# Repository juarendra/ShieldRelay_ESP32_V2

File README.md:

# ShieldRelay_ESP32
Multiple Relay with ESP32 shield. In board there are 5 Relay and 3 type of Relay, first is 30A Relay Coil, second is 10 A Relay Coil and third is SSR 2A. And there are full extend header of Microcontroller. the power using Stepdown LM2596 with output 5V 3A and Input 5-30VDC. 

## Spesification ShieldRelay_ESP32
- Input Power 5-30VDC and stepdown to 5VDC
- PTC Fuse
- INPUT HEADER
- VCC HEADER
- VCC Selector 3v3 or 5V
- ESP32 WROON on BOARD
- Pin Header GPIO with Servo Formated
- 1 x 30A Relay Coil
- 2 x 10A Relay Coil
- 2 x 2A SSR

# Privew Hardware BASE RPI

# Privew Hardware BASE RPI

# Documentation 
- [Dimension](https://github.com/juarendra/ShieldRelay_ESP32_V2/blob/main/HARDWARE/dimension_shield_esp32_v2.pdf)
- [BOM](https://github.com/juarendra/ShieldRelay_ESP32_V2/blob/main/DOC/shieldRelayV2.csv)

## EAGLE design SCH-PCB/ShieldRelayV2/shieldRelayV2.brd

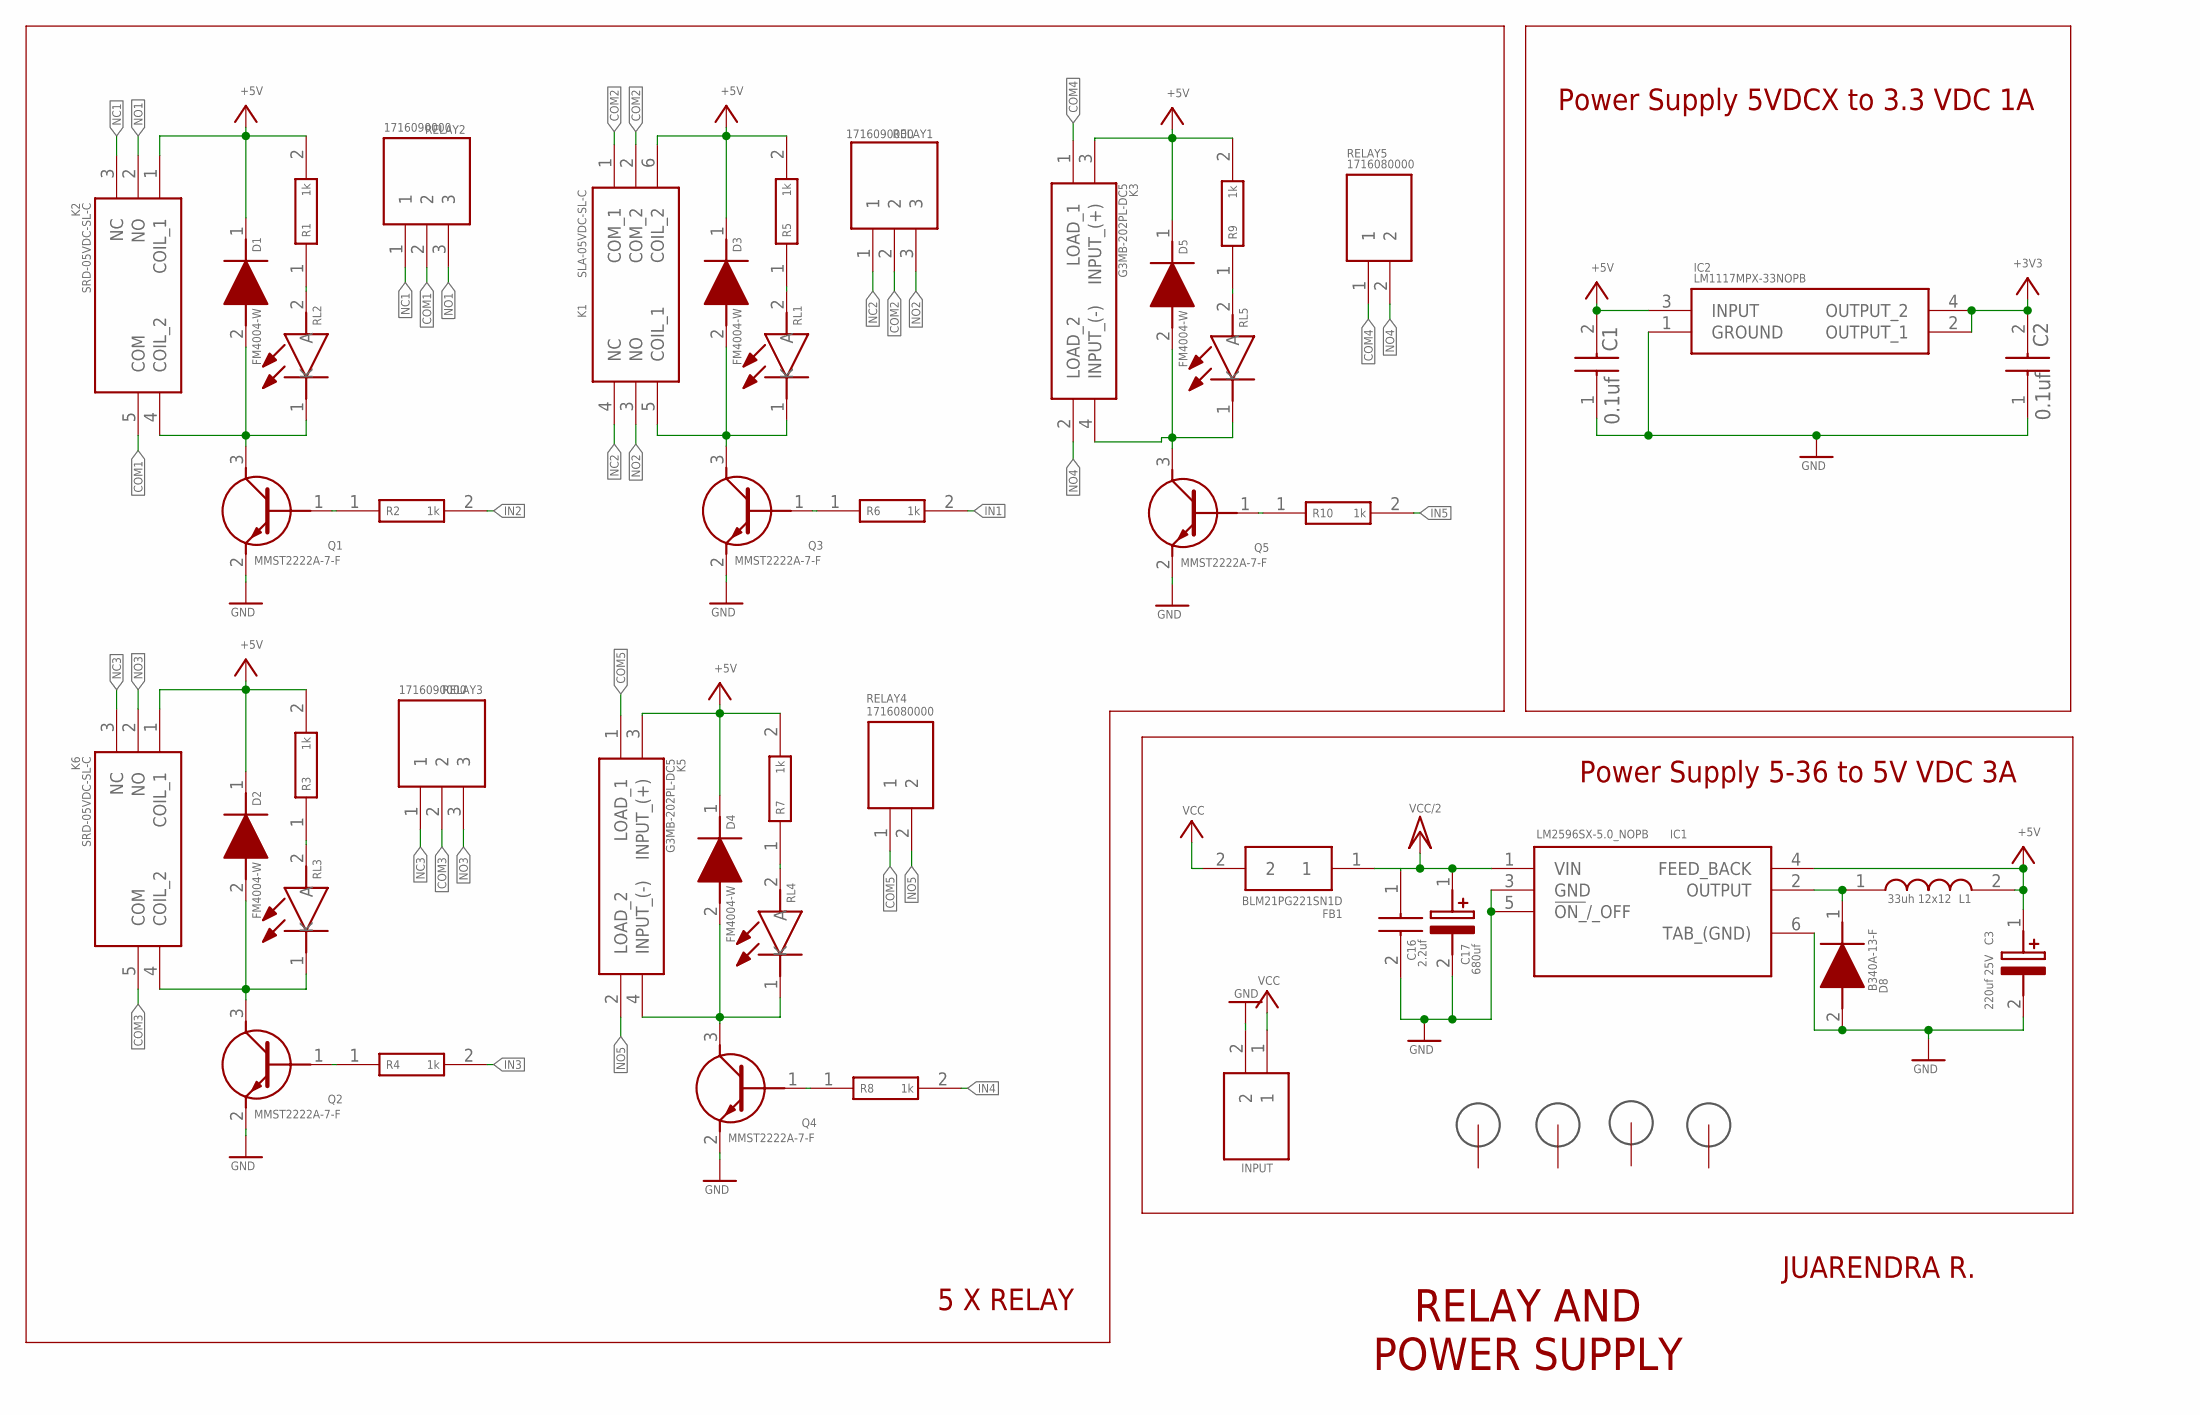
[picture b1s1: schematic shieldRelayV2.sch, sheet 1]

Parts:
C1, C2: 0.1uf; CAPC1608X95N
C3: 220uf 25V; CAPPRD350W60D850H1250
C16: 2.2uf; CAPC2012X140N
C17: 680uf; EEHZS1H221P
D1, D2, D3, D4, D5: FM4004-W; DIONM5025X231N
D8: B340A-13-F; DIOM5226X240N
FB1: BLM21PG221SN1D; BEADC2012X105N
H1, H2, H3, H4: 3MM_HOLE
IC1: LM2596SX-5.0_NOPB; KTT0005B
IC2: LM1117MPX-33NOPB; SOT230P700X180-4N
INPUT: 1759017; SHDRRA2W103P0X508_1X2_1016X120
K1: SLA-05VDC-SL-C; SLA05VDCSLC
K2, K6: SRD-05VDC-SL-C; SRD05VDCSLC
K3, K5: G3MB-202PL-DC5; G3MB202PLDC5
L1: 33uh 12x12; WE-PD_1260/1245/1280/121054
Q1, Q2, Q3, Q4, Q5: MMST2222A-7-F; SOT65P210X110-3N
R1, R2, R3, R4, R5, R6, R7, R8, R9, R10: 1k; ERA3AEB101V
RELAY1, RELAY2, RELAY3: 1716090000; SHDR3W95P0X508_1X3_1524X1000X1
RELAY4, RELAY5: 1716080000
RL1, RL2, RL3, RL4, RL5: 150080SS75000; LEDC2012X80N

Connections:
+3V3: C2.2, IC2.2 (OUTPUT_1), IC2.4 (OUTPUT_2); also elsewhere on the board
+5V: C1.2, C3.1 (+), D1.1 (K), D2.1 (K), D3.1 (K), D4.1 (K), D5.1 (K), IC1.4 (FEED_BACK), IC2.3 (INPUT), K1.6 (COIL_2), K2.1 (COIL_1), K3.3 (INPUT_(+)), K5.3 (INPUT_(+)), K6.1 (COIL_1), L1.2, R1.2, R3.2, R5.2, R7.2, R9.2; also elsewhere on the board
COM1: K2.5 (COM), RELAY2.2
COM2: K1.1 (COM_1), K1.2 (COM_2), RELAY1.2
COM3: K6.5 (COM), RELAY3.2
COM4: K3.1 (LOAD_1), RELAY5.1
COM5: K5.1 (LOAD_1), RELAY4.1
GND: C1.1, C2.1, C3.2 (-), C16.2, C17.2 (-), D8.2 (A), IC1.3 (GND), IC1.5 (!ON_!/_OFF), IC1.6 (TAB_(GND)), IC2.1 (GROUND), INPUT.2, Q1.2 (E), Q2.2 (E), Q3.2 (E), Q4.2 (E), Q5.2 (E); also elsewhere on the board
IN1: R6.2; also elsewhere on the board
IN2: R2.2; also elsewhere on the board
IN3: R4.2; also elsewhere on the board
IN4: R8.2; also elsewhere on the board
IN5: R10.2; also elsewhere on the board
unnamed: R3.1, RL3.2 (A)
unnamed: R1.1, RL2.2 (A)
unnamed: D1.2 (A), K2.4 (COIL_2), Q1.3 (C), RL2.1 (K)
unnamed: Q2.1 (B), R4.1
unnamed: D2.2 (A), K6.4 (COIL_2), Q2.3 (C), RL3.1 (K)
unnamed: R5.1, RL1.2 (A)
unnamed: D3.2 (A), K1.5 (COIL_1), Q3.3 (C), RL1.1 (K)
unnamed: Q1.1 (B), R2.1
unnamed: R7.1, RL4.2 (A)
unnamed: D4.2 (A), K5.4 (INPUT_(-)), Q4.3 (C), RL4.1 (K)
unnamed: Q4.1 (B), R8.1
unnamed: R9.1, RL5.2 (A)
unnamed: D5.2 (A), K3.4 (INPUT_(-)), Q5.3 (C), RL5.1 (K)
unnamed: Q3.1 (B), R6.1
unnamed: D8.1 (K), IC1.2 (OUTPUT), L1.1
unnamed: Q5.1 (B), R10.1
NC1: K2.3 (NC), RELAY2.1
NC2: K1.4 (NC), RELAY1.1
NC3: K6.3 (NC), RELAY3.1
NO1: K2.2 (NO), RELAY2.3
NO2: K1.3 (NO), RELAY1.3
NO3: K6.2 (NO), RELAY3.3
NO4: K3.2 (LOAD_2), RELAY5.2
NO5: K5.2 (LOAD_2), RELAY4.2
VCC: FB1.2, INPUT.1
VCC/2: C16.1, C17.1 (+), FB1.1, IC1.1 (VIN); also elsewhere on the board

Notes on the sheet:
Power Supply 5-36 to 5V VDC 3A
5 X RELAY
Power Supply 5VDCX to 3.3 VDC 1A
RELAY AND POWER SUPPLY
JUARENDRA R.

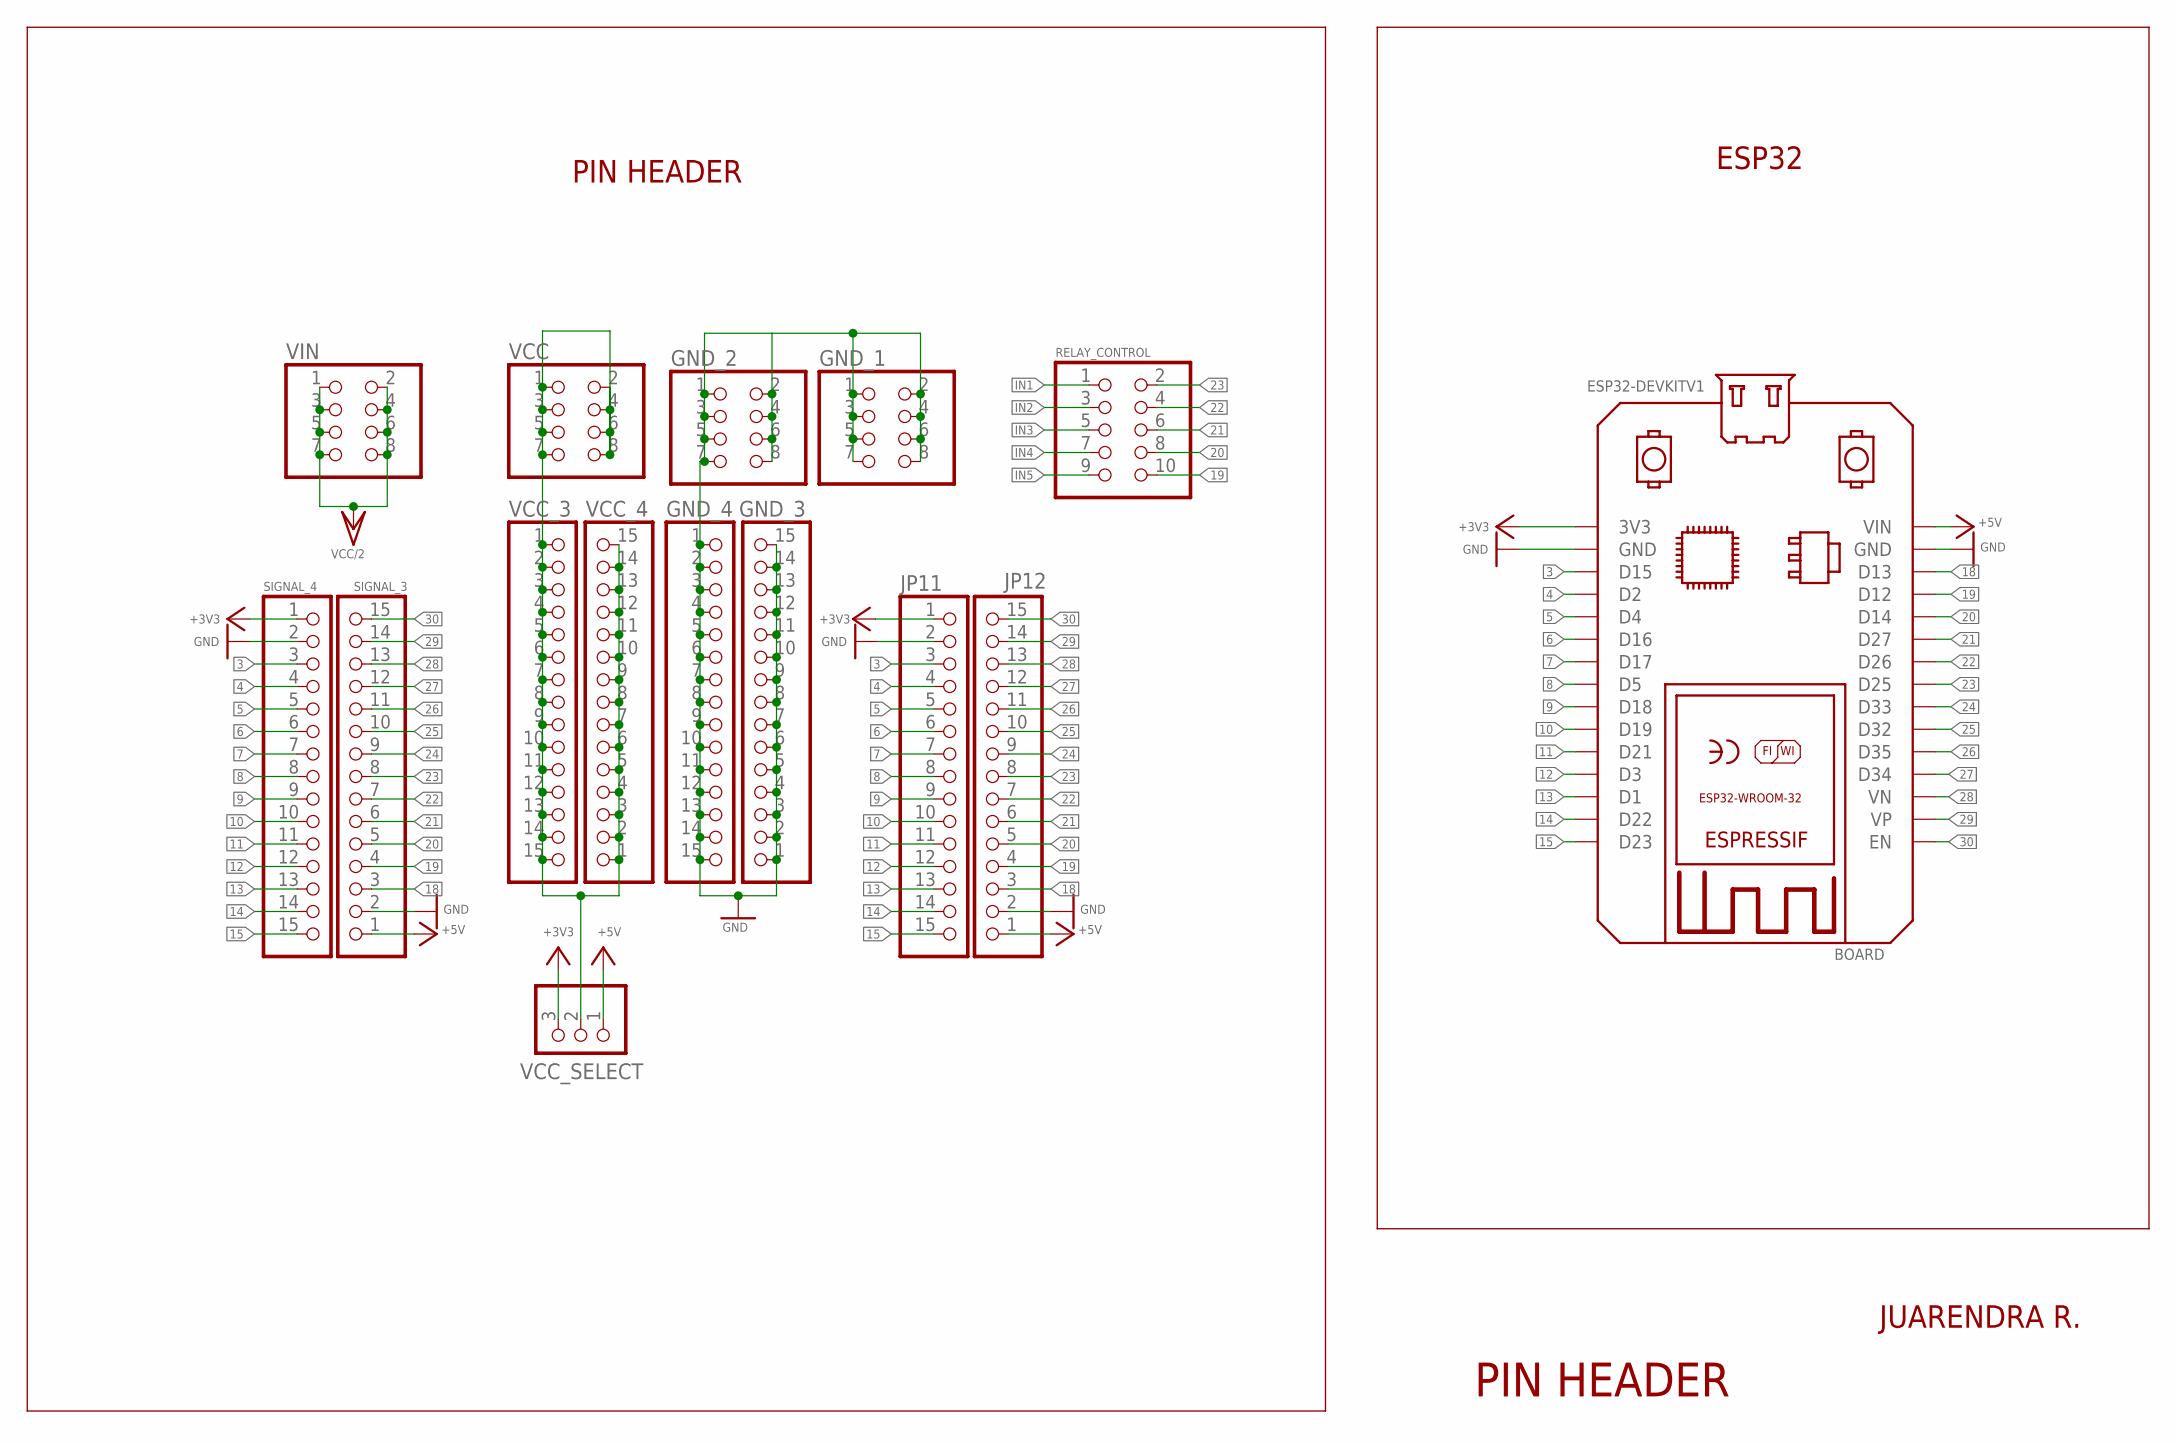
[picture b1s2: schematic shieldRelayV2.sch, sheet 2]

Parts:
BOARD: ESP32DEVKITV1; ESP32-DEVKITV1
GND_1, GND_2: PINHD-2X4; 2X04
GND_3, GND_4: PINHD-1X15; 1X15
JP11, JP12: PINHD-1X15; 1X15
RELAY_CONTROL: PINHD-2X5; 2X05
SIGNAL_3, SIGNAL_4: PINHD-1X15; 1X15
VCC: PINHD-2X4; 2X04
VCC_3, VCC_4: PINHD-1X15; 1X15
VCC_SELECT: PINHD-1X3; 1X03
VIN: PINHD-2X4; 2X04

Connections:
3: BOARD.D15, JP11.3, SIGNAL_4.3; also elsewhere on the board
4: BOARD.D2, JP11.4, SIGNAL_4.4; also elsewhere on the board
5: BOARD.D4, JP11.5, SIGNAL_4.5; also elsewhere on the board
6: BOARD.D16, JP11.6, SIGNAL_4.6; also elsewhere on the board
7: BOARD.D17, JP11.7, SIGNAL_4.7; also elsewhere on the board
8: BOARD.D5, JP11.8, SIGNAL_4.8; also elsewhere on the board
9: BOARD.D18, JP11.9, SIGNAL_4.9; also elsewhere on the board
10: BOARD.D19, JP11.10, SIGNAL_4.10; also elsewhere on the board
11: BOARD.D21, JP11.11, SIGNAL_4.11; also elsewhere on the board
12: BOARD.D3, JP11.12, SIGNAL_4.12; also elsewhere on the board
13: BOARD.D1, JP11.13, SIGNAL_4.13; also elsewhere on the board
14: BOARD.D22, JP11.14, SIGNAL_4.14; also elsewhere on the board
15: BOARD.D23, JP11.15, SIGNAL_4.15; also elsewhere on the board
18: BOARD.D13, JP12.3, SIGNAL_3.3; also elsewhere on the board
19: BOARD.D12, JP12.4, RELAY_CONTROL.10, SIGNAL_3.4; also elsewhere on the board
20: BOARD.D14, JP12.5, RELAY_CONTROL.8, SIGNAL_3.5; also elsewhere on the board
21: BOARD.D27, JP12.6, RELAY_CONTROL.6, SIGNAL_3.6; also elsewhere on the board
22: BOARD.D26, JP12.7, RELAY_CONTROL.4, SIGNAL_3.7; also elsewhere on the board
23: BOARD.D25, JP12.8, RELAY_CONTROL.2, SIGNAL_3.8; also elsewhere on the board
24: BOARD.D33, JP12.9, SIGNAL_3.9; also elsewhere on the board
25: BOARD.D32, JP12.10, SIGNAL_3.10; also elsewhere on the board
26: BOARD.D35, JP12.11, SIGNAL_3.11; also elsewhere on the board
27: BOARD.D34, JP12.12, SIGNAL_3.12; also elsewhere on the board
28: BOARD.VN, JP12.13, SIGNAL_3.13; also elsewhere on the board
29: BOARD.VP, JP12.14, SIGNAL_3.14; also elsewhere on the board
30: BOARD.EN, JP12.15, SIGNAL_3.15; also elsewhere on the board
+3V3: BOARD.3V3, JP11.1, SIGNAL_4.1, VCC_SELECT.3; also elsewhere on the board
+5V: BOARD.VIN, JP12.1, SIGNAL_3.1, VCC_SELECT.1; also elsewhere on the board
GND: BOARD.GND, BOARD.GND@1 (GND), GND_1.1, GND_1.2, GND_1.3, GND_1.4, GND_1.5, GND_1.6, GND_1.7, GND_1.8, GND_2.1, GND_2.2, GND_2.3, GND_2.4, GND_2.5, GND_2.6, GND_2.7, GND_2.8, GND_3.1, GND_3.2, GND_3.3, GND_3.4, GND_3.5, GND_3.6, GND_3.7, GND_3.8, GND_3.9, GND_3.10, GND_3.11, GND_3.12, GND_3.13, GND_3.14, GND_3.15, GND_4.1, GND_4.2, GND_4.3, GND_4.4, GND_4.5, GND_4.6, GND_4.7, GND_4.8, GND_4.9, GND_4.10, GND_4.11, GND_4.12, GND_4.13, GND_4.14, GND_4.15, JP11.2, JP12.2, SIGNAL_3.2, SIGNAL_4.2; also elsewhere on the board
IN1: RELAY_CONTROL.1; also elsewhere on the board
IN2: RELAY_CONTROL.3; also elsewhere on the board
IN3: RELAY_CONTROL.5; also elsewhere on the board
IN4: RELAY_CONTROL.7; also elsewhere on the board
IN5: RELAY_CONTROL.9; also elsewhere on the board
unnamed: VCC.1, VCC.2, VCC.3, VCC.4, VCC.5, VCC.6, VCC.7, VCC.8, VCC_3.1, VCC_3.2, VCC_3.3, VCC_3.4, VCC_3.5, VCC_3.6, VCC_3.7, VCC_3.8, VCC_3.9, VCC_3.10, VCC_3.11, VCC_3.12, VCC_3.13, VCC_3.14, VCC_3.15, VCC_4.1, VCC_4.2, VCC_4.3, VCC_4.4, VCC_4.5, VCC_4.6, VCC_4.7, VCC_4.8, VCC_4.9, VCC_4.10, VCC_4.11, VCC_4.12, VCC_4.13, VCC_4.14, VCC_4.15, VCC_SELECT.2
VCC/2: VIN.1, VIN.2, VIN.3, VIN.4, VIN.5, VIN.6, VIN.7, VIN.8; also elsewhere on the board

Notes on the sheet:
PIN HEADER
JUARENDRA R.
ESP32

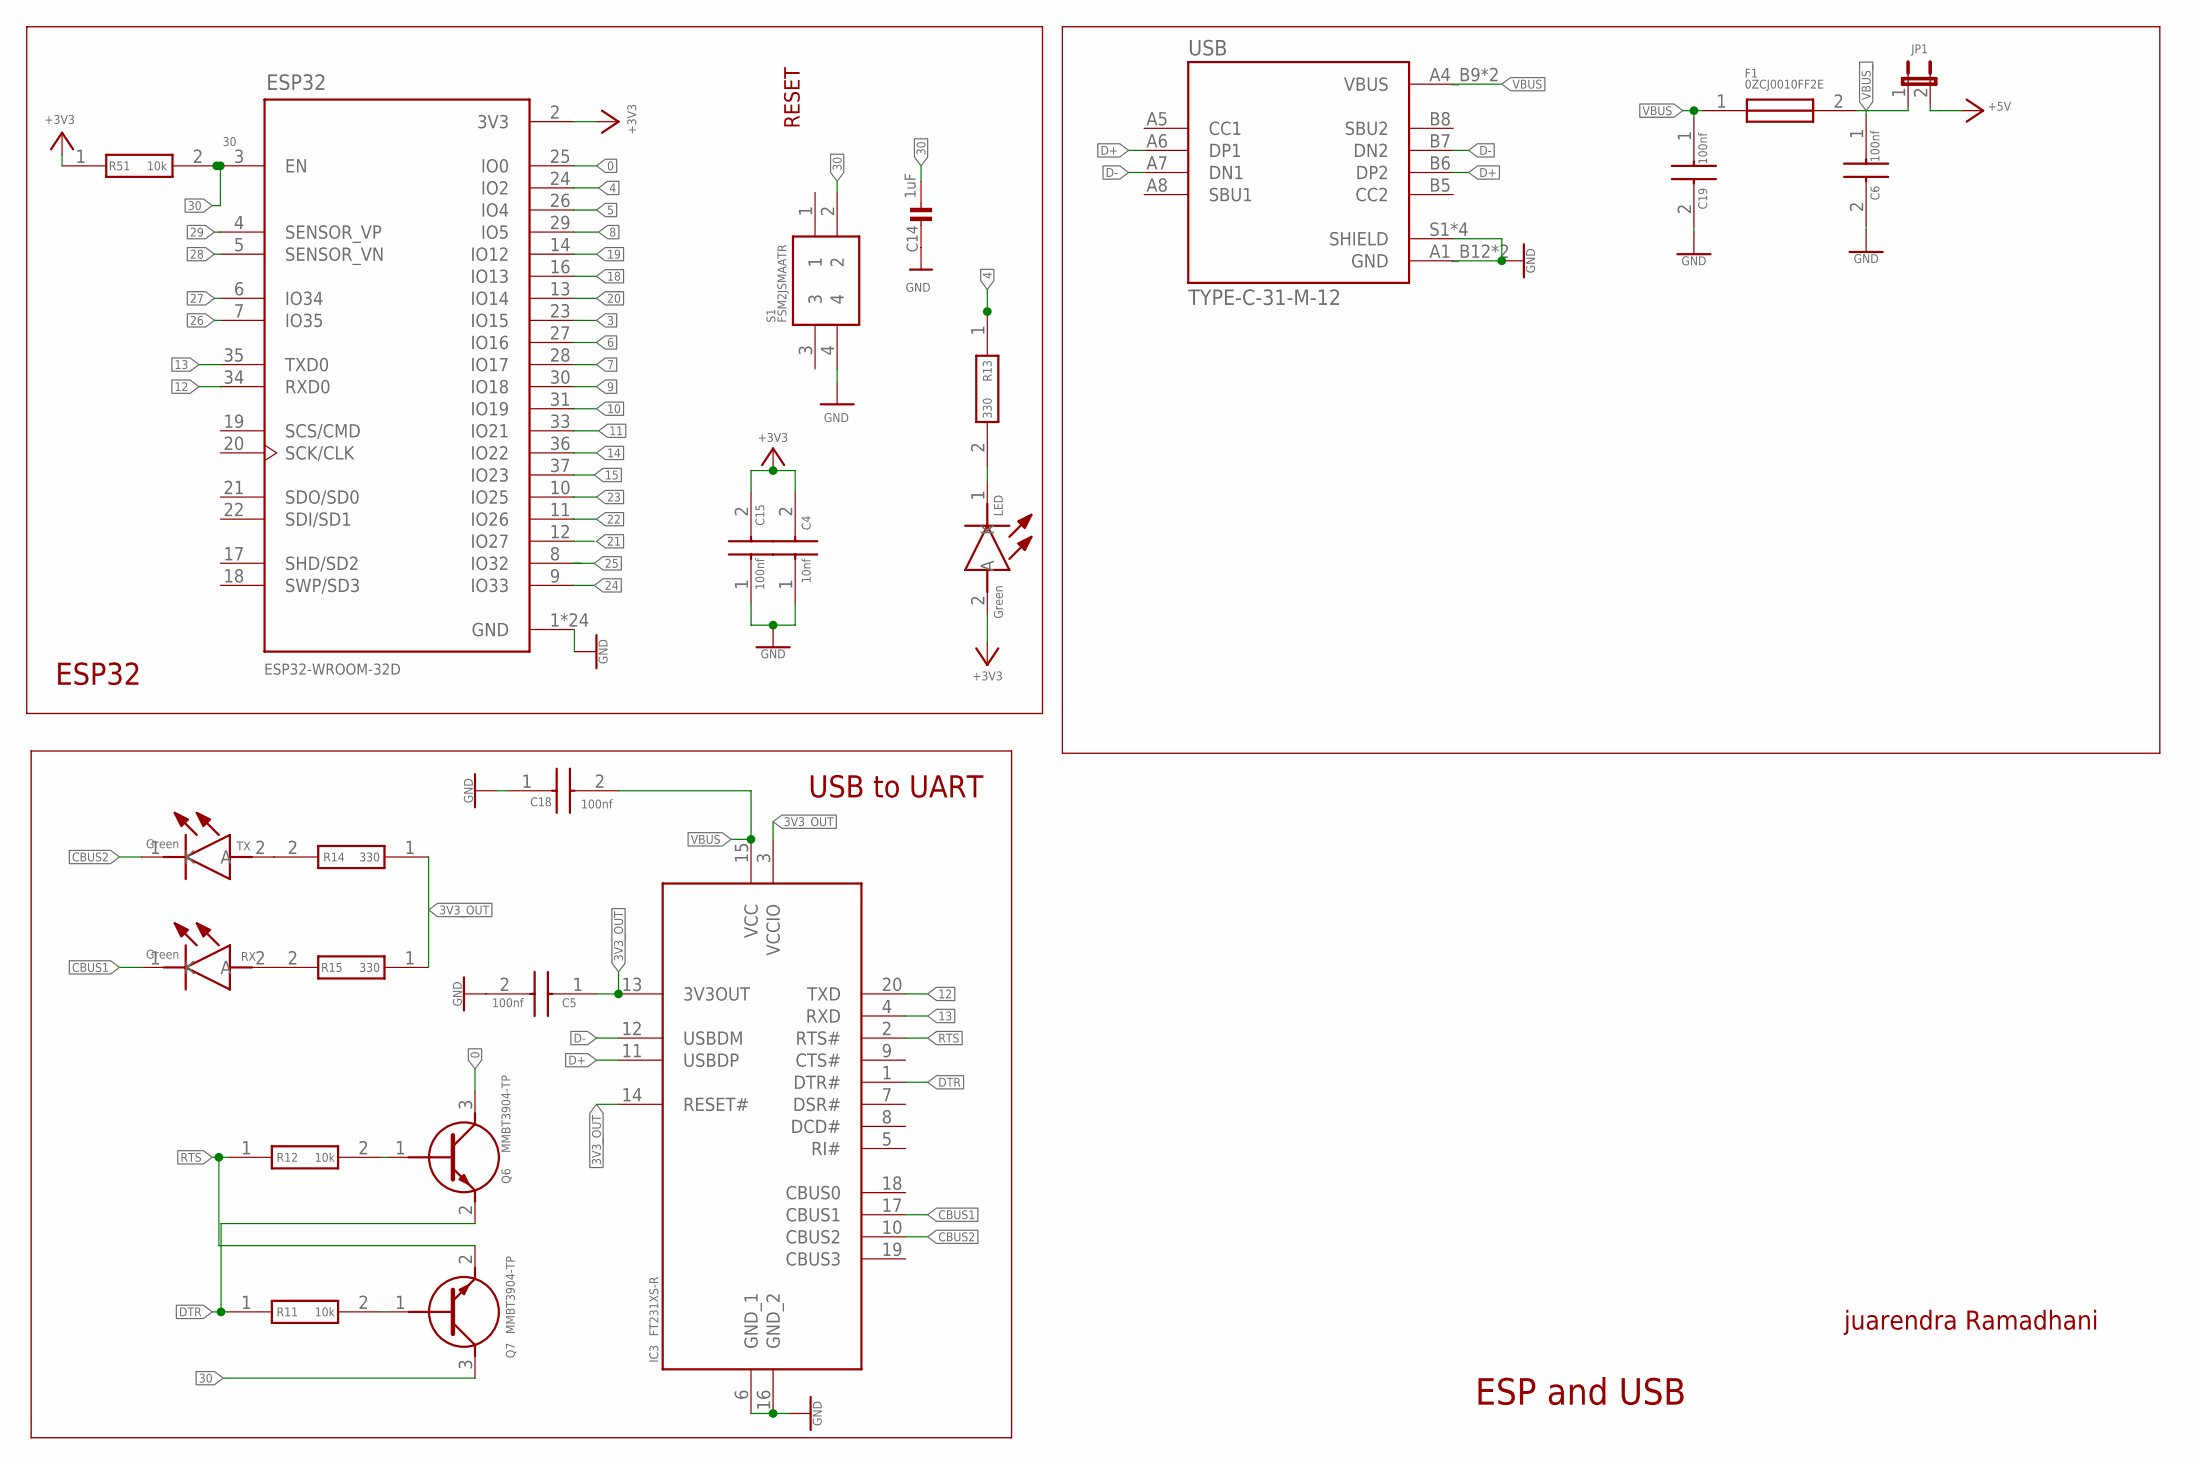
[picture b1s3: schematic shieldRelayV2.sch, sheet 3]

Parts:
C4: 10nf; CAPC1608X87N
C5, C6, C15, C18, C19: 100nf; CAPC1608X87N
C14: 1uF; 0603
ESP32: ESP32-WROOM-32D; MODULE_ESP32-WROOM-32D
F1: 0ZCJ0010FF2E; FUSC3216X75N
IC3: FT231XS-R; SOP64P599X175-20N
JP1: JP1E; JP1
LED: Green; LEDC2012X80N
Q6, Q7: MMBT3904-TP; SI2305TP
R11, R12, R51: 10k; RESC1608X55N
R13, R14, R15: 330; ERJH3
RX: Green; LEDC2012X80N
S1: FSM2JSMAATR; FSM2J_1
TX: Green; LEDC2012X80N
USB: TYPE-C-31-M-12; HRO_TYPE-C-31-M-12

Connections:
0: ESP32.25 (IO0), Q6.3 (C)
3: ESP32.23 (IO15); also elsewhere on the board
3V3_OUT: C5.1, IC3.3 (VCCIO), IC3.13 (3V3OUT), IC3.14 (RESET#), R14.1, R15.1
4: ESP32.24 (IO2), R13.1; also elsewhere on the board
5: ESP32.26 (IO4); also elsewhere on the board
6: ESP32.27 (IO16); also elsewhere on the board
7: ESP32.28 (IO17); also elsewhere on the board
8: ESP32.29 (IO5); also elsewhere on the board
9: ESP32.30 (IO18); also elsewhere on the board
10: ESP32.31 (IO19); also elsewhere on the board
11: ESP32.33 (IO21); also elsewhere on the board
12: ESP32.34 (RXD0), IC3.20 (TXD); also elsewhere on the board
13: ESP32.35 (TXD0), IC3.4 (RXD); also elsewhere on the board
14: ESP32.36 (IO22); also elsewhere on the board
15: ESP32.37 (IO23); also elsewhere on the board
18: ESP32.16 (IO13); also elsewhere on the board
19: ESP32.14 (IO12); also elsewhere on the board
20: ESP32.13 (IO14); also elsewhere on the board
21: ESP32.12 (IO27); also elsewhere on the board
22: ESP32.11 (IO26); also elsewhere on the board
23: ESP32.10 (IO25); also elsewhere on the board
24: ESP32.9 (IO33); also elsewhere on the board
25: ESP32.8 (IO32); also elsewhere on the board
26: ESP32.7 (IO35); also elsewhere on the board
27: ESP32.6 (IO34); also elsewhere on the board
28: ESP32.5 (SENSOR_VN); also elsewhere on the board
29: ESP32.4 (SENSOR_VP); also elsewhere on the board
30: C14.1, ESP32.3 (EN), Q7.3 (C), R51.2, S1.2; also elsewhere on the board
+3V3: C4.2, C15.2, ESP32.2 (3V3), LED.2 (A), R51.1; also elsewhere on the board
+5V: JP1.2; also elsewhere on the board
CBUS1: IC3.17 (CBUS1), RX.1 (K)
CBUS2: IC3.10 (CBUS2), TX.1 (K)
D+: IC3.11 (USBDP), USB.A6 (DP1), USB.B6 (DP2)
D-: IC3.12 (USBDM), USB.A7 (DN1), USB.B7 (DN2)
DTR: IC3.1 (DTR#), Q6.2 (E), R11.1
GND: C4.1, C5.2, C6.2, C14.2, C15.1, C18.1, C19.2, ESP32.1 (GND), ESP32.15 (GND), ESP32.38 (GND), ESP32.39_1 (GND), ESP32.39_2 (GND), ESP32.39_3 (GND), ESP32.39_4 (GND), ESP32.39_5 (GND), ESP32.39_6 (GND), ESP32.39_7 (GND), ESP32.39_8 (GND), ESP32.39_9 (GND), ESP32.39_10 (GND), ESP32.39_11 (GND), ESP32.39_12 (GND), ESP32.39_13 (GND), ESP32.39_14 (GND), ESP32.39_15 (GND), ESP32.39_16 (GND), ESP32.39_17 (GND), ESP32.39_18 (GND), ESP32.39_19 (GND), ESP32.39_20 (GND), ESP32.39_21 (GND), IC3.6 (GND_1), IC3.16 (GND_2), S1.4, USB.A1_B12 (GND), USB.B1_A12 (GND), USB.S1 (SHIELD), USB.S2 (SHIELD), USB.S3 (SHIELD), USB.S4 (SHIELD); also elsewhere on the board
unnamed: Q7.1 (B), R11.2
unnamed: Q6.1 (B), R12.2
unnamed: R15.2, RX.2 (A)
unnamed: R14.2, TX.2 (A)
unnamed: LED.1 (K), R13.2
RTS: IC3.2 (RTS#), Q7.2 (E), R12.1
VBUS: C18.2, C19.1, F1.1, IC3.15 (VCC), USB.A4_B9 (VBUS), USB.B4_A9 (VBUS)
VBUS_: C6.1, F1.2, JP1.1

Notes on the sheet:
RESET
ESP32
USB to UART
ESP and USB
juarendra Ramadhani

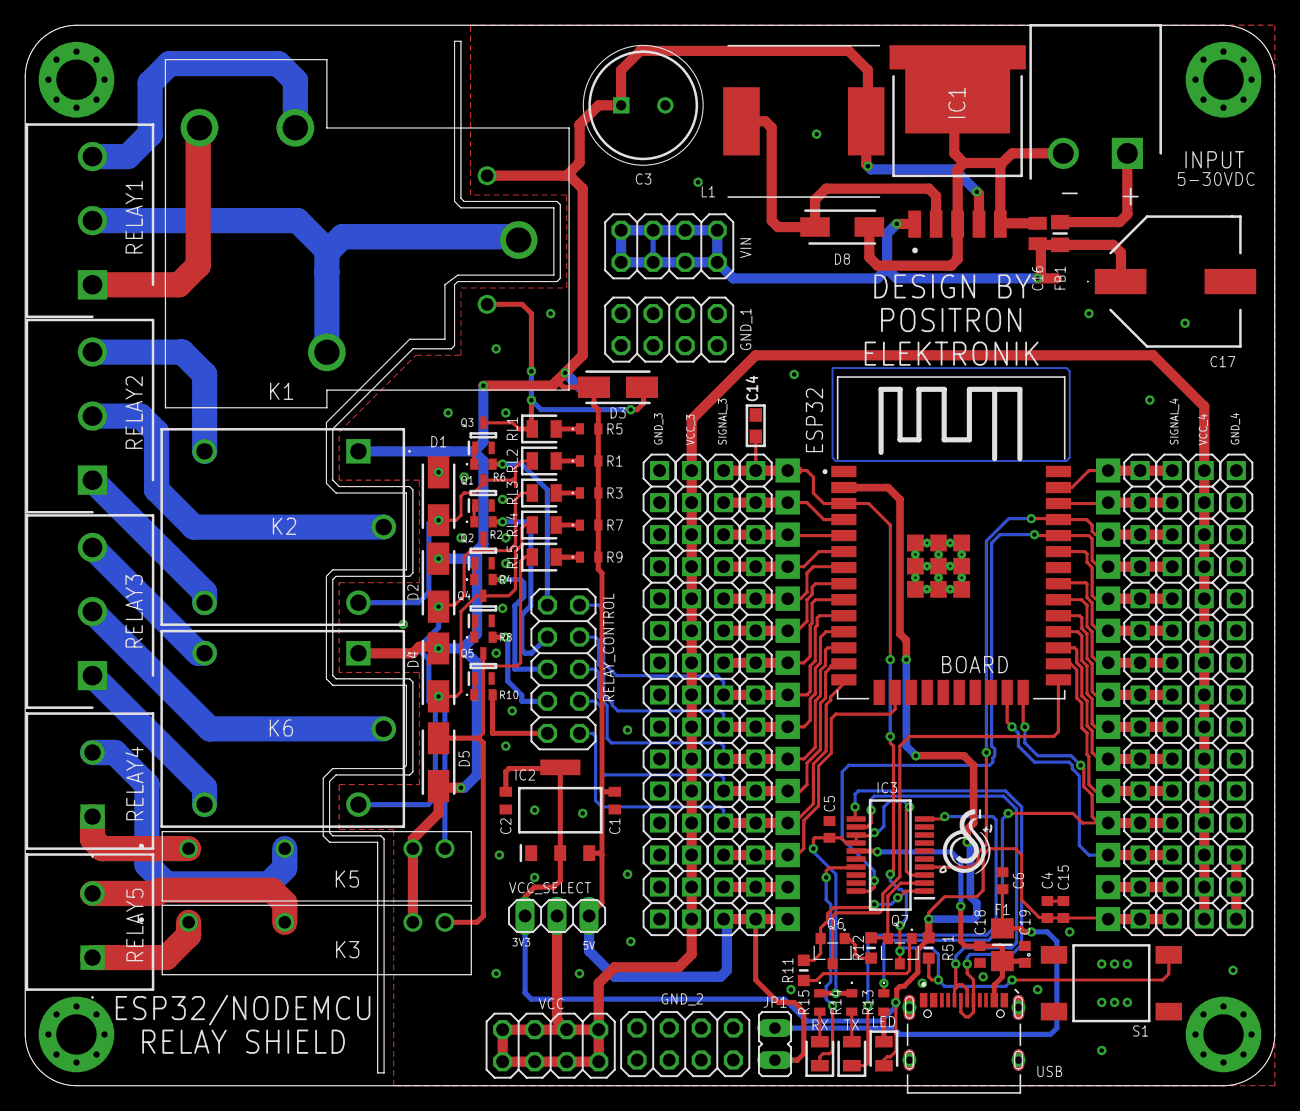
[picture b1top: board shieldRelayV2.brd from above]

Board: 2 copper layers, 99.1 x 84.1 mm, 89 parts (1 on the bottom side), 81 nets.

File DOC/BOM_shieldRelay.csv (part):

"Qty";"Value";"Device";"Package";"Parts";"Description";"ARROW_PART_NUMBER";"ARROW_PRICE-STOCK";"DESCRIPTION";"DIGIKEY_PARTNUMBER";"DIGIKEY_PRICE-STOCK";"ESP32-DEVKITV1";"HEIGHT";"MANUFACTURER_NAME";"MANUFACTURER_PART_NUMBER";"MOUSER_PART_NUMBER";"MOUSER_PRICE-STOCK";"POPULARITY";
"9";"";"PINHD-1X15";"1X15";"GND_3, GND_4, JP11, JP12, JP13, SIGNAL_3, SIGNAL_4, VCC_3, VCC_4";"PIN HEADER";"";"";"";"";"";"";"";"";"";"";"";"4";
"1";"";"PINHD-1X3";"1X03";"VCC_SELECT";"PIN HEADER";"";"";"";"";"";"";"";"";"";"";"";"92";
"4";"";"PINHD-2X4";"2X04";"GND_1, GND_2, VCC, VIN";"PIN HEADER";"";"";"";"";"";"";"";"";"";"";"";"47";
"1";"";"PINHD-2X5";"2X05";"RELAY_CONTROL";"PIN HEADER";"";"";"";"";"";"";"";"";"";"";"";"35";
"2";"0.1uf";"KGM15BR71E104KT";"CAPC1608X95N";"C1, C2";"0603 25 V X7R 100nF +/-10%";"";"";"0603 25 V X7R 100nF +/-10%";"";"";"";"0.95mm";"Kyocera AVX";"KGM15BR71E104KT";"581-KGM15BR71E104KT";"https://www.mouser.co.uk/ProductDetail/KYOCERA-AVX/KGM15BR71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";"";
"5";"150080SS75000";"150080SS75000";"LEDC2012X80N";"RL1, RL2, RL3, RL4, RL5";"Wurth Elektronik 150080SS75000, WL-SMCW Series Red LED, 630 nm, 2012 (0805) Clear, Rectangle Lens SMD Package";"";"";"Wurth Elektronik 150080SS75000, WL-SMCW Series Red LED, 630 nm, 2012 (0805) Clear, Rectangle Lens SMD Package";"732-4985-1-ND";"https://www.digikey.com/product-detail/en/w%C3%BCrth-elektro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";"";"0.8mm";"Wurth Elektronik";"150080SS75000";"710-150080SS75000";"https://www.mouser.co.uk/ProductDetail/Wurth-Elektronik/1500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";"";
"2";"1716080000";"1716080000";"1716080000";"RELAY4, RELAY5";"Printed circuit board terminals, 5.08 mm, Number of poles: 2, 90, Solder pin length: 3.5 mm, tinned, orange, Clamping yoke connection, Clamping range, max. [rated connection]: 2.5 mm, Box";"";"";"Printed circuit board terminals, 5.08 mm, Number of poles: 2, 90, Solder pin length: 3.5 mm, tinned, orange, Clamping yoke connection, Clamping range, max. [rated connection]: 2.5 mm, Box";"";"";"";"13.8mm";"Weidmuller";"1716080000";"470-1716080000";"https://www.mouser.co.uk/ProductDetail/Weidmuller/1716080000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";"";
"3";"1716090000";"1716090000";"SHDR3W95P0X508_1X3_1524X1000X1";"RELAY1, RELAY2, RELAY3";"Printed circuit board terminals, 5.08 mm, Number of poles: 3, 90, Solder pin length: 3.5 mm, tinned, orange, Clamping yoke connection, Clamping range, max. [rated connection]: 2.5 mm, Box";"";"";"Printed circuit board terminals, 5.08 mm, Number of poles: 3, 90, Solder pin length: 3.5 mm, tinned, orange, Clamping yoke connection, Clamping range, max. [rated connection]: 2.5 mm, Box";"";"";"";"13.8mm";"Weidmuller";"1716090000";"470-1716090000";"https://www.mouser.co.uk/ProductDetail/Weidmuller/1716090000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";"";
"1";"1759017";"1759017";"SHDRRA2W103P0X508_1X2_1016X120";"INPUT";"PCB header, nominal cross section: 2.5 mm?, color: green, nominal current: 12 A, rated voltage (III/2): 320 V, contact surface: Tin, type of contact: Male connector, Number of potentials: 2, Number of rows: 1, Number of positions per row: 2, number of connections: 2, product range: MSTB 2,5/..-G, pitch: 5.08 mm, mounting: Wave soldering, pin layout: Linear pinning, solder pin [P]: 3.5 mm, Stecksystem: CLASSIC COMBICON, Locking: without, type of packaging: packed in cardboard";"";"";"PCB header, nominal cross section: 2.5 mm?, color: green, nominal current: 12 A, rated voltage (III/2): 320 V, contact surface: Tin, type of contact: Male connector, Number of potentials: 2, Number of rows: 1, Number of positions per row: 2, number of connections: 2, product range: MSTB 2,5/..-G, pitch: 5.08 mm, mounting: Wave soldering, pin layout: Linear pinning, solder pin [P]: 3.5 mm, Stecksystem: CLASSIC COMBICON, Locking: without, type of packaging: packed in cardboard";"";"";"";"8.72mm";"Phoenix Contact";"1759017";"651-1759017";"https://www.mouser.co.uk/ProductDetail/Phoenix-Contact/17590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";"";
"10";"1k";"ERA-3AED102V";"ERA3AEB101V";"R1, R2, R3, R4, R5, R6, R7, R8, R9, R10";"Thin Film Resistors - SMD 0603 1000ohms 25ppm 0.5% AEC-Q200";"";"";"Thin Film Resistors - SMD 0603 1000ohms 25ppm 0.5% AEC-Q200";"";"";"";"0.55mm";"Panasonic";"ERA-3AED102V";"667-ERA-3AED102V";"https://www.mouser.co.uk/ProductDetail/Panasonic/ERA-3AED102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";"";
"1";"2.2uf";"KAF21KR71H225KU";"CAPC2012X140N";"C16";"Multilayer Ceramic Capacitors MLCC - SMD/SMT 50V 2.2uF X7R 0805 10% AEC-Q200 FLEXITERM";"";"";"Multilayer Ceramic Capacitors MLCC - SMD/SMT 50V 2.2uF X7R 0805 10% AEC-Q200 FLEXITERM";"";"";"";"1.4mm";"Kyocera AVX";"KAF21KR71H225KU";"581-KAF21KR71H225KU";"https://www.mouser.co.uk/ProductDetail/KYOCERA-AVX/KAF21KR71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";"";
"1";"220uf 25V";"MAL203836221E3";"CAPPRD350W60D850H1250";"C3";"VISHAY - MAL203836221E3 - CAP, 220F, 25V, 20%";"";"";"VISHAY - MAL203836221E3 - CAP, 220F, 25V, 20%";"";"";"";"12.5mm";"Vishay";"MAL203836221E3";"594-MAL203836221E3";"https://www.mouser.co.uk/ProductDetail/Vishay-BC-Components/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";"";
"1";"33uh 12x12";"744770133";"WE-PD_1260/1245/1280/121054";"L1";"Wurth WE-PD Series Shielded Wire-wound SMD Inductor with a Ferrite Core, 33 uH +/-20% 3.6A Idc";"";"";"Wurth WE-PD Series Shielded Wire-wound SMD Inductor with a Ferrite Core, 33 uH +/-20% 3.6A Idc";"";"";"";"mm";"Wurth Elektronik";"744770133";"710-744770133";"https://www.mouser.co.uk/ProductDetail/Wurth-Elektronik/7447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";"";
"4";"3MM_HOLE";"3MM_HOLE";"3MM_HOLE";"H1, H2, H3, H4";"Cool looking 3mm hole with ground connection";"";"";"";"";"";"";"";"";"";"";"";"";
"1";"680uf";"EEH-ZU1V681UP";"EEHZS1H221P";"C17";"Conductive Polymer Hybrid Aluminum Electrolytic Capacitor";"";"";"Conductive Polymer Hybrid Aluminum Electrolytic Capacitor";"";"";"";"10.5mm";"Panasonic";"EEH-ZU1V681UP";"667-EEH-ZU1V681UP";"https://www.mouser.co.uk/ProductDetail/Panasonic/EEH-ZU1V681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";"";
"1";"B340A-13-F";"B340A-13-F";"DIOM5226X240N";"D8";"Schottky Diode 3A 40V 0.5Vf SMA Diodes Inc B340A-13-F, SMT Schottky Diode, 40V 3A, 2-Pin DO-214AC";"";"";"Schottky Diode 3A 40V 0.5Vf SMA Diodes Inc B340A-13-F, SMT Schottky Diode, 40V 3A, 2-Pin DO-214AC";"";"";"";"2.4mm";"Diodes Incorporated";"B340A-13-F";"621-B340A-F";"https://www.mouser.co.uk/ProductDetail/Diodes-Incorporated/B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";"";
"1";"BLM21PG221SN1D";"BLM21PG221SN1D";"BEADC2012X105N";"FB1";"Murata Ferrite Bead (Chip Ferrite Bead), 2 x 1.25 x 0.85mm";"";"";"Murata Ferrite Bead (Chip Ferrite Bead), 2 x 1.25 x 0.85mm";"";"";"";"1.05mm";"Murata Electronics";"BLM21PG221SN1D";"81-BLM21P221SG";"https://www.mouser.co.uk/ProductDetail/Murata-Electronics/BL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";"";
"1";"ESP32DEVKITV1";"ESP32DEVKITV1";"ESP32-DEVKITV1";"BOARD";"https://github.com/shridattdudhat";"";"";"";"";"";"";"";"";"";"";"";"";
"5";"FM4004-W";"FM4004-W";"DIONM5025X231N";"D1, D2, D3, D4, D5";"Rectifiers 1N4004 1A 400V";"";"";"Rectifiers 1N4004 1A 400V";"";"";"";"2.31mm";"Rectron";"FM4004-W";"583-FM4004";"https://www.mouser.co.uk/ProductDetail/Rectron/FM4004-W?qs=I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";"";
"2";"G3MB-202PL-DC5";"G3MB-202PL-DC5";"G3MB202PLDC5";"K3, K5";"Solid State Relays - PCB Mount 5VDC/100-240VAC 2A";"";"";"Solid State Relays - PCB Mount 5VDC/100-240VAC 2A";"";"";"";"20.5mm";"Omron Electronics";"G3MB-202PL-DC5";"653-G3MB-202PL-DC5";"https://www.mouser.co.uk/ProductDetail/Omron-Automation-and-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";"";
"1";"LM1117MPX-33NOPB";"LM1117MPX-33NOPB";"SOT230P700X180-4N";"IC2";"LDO Voltage Regulators 800-mA 15-V linear voltage regulator 800-mA 15-V linear voltage regulator";"";"";"LDO Voltage Regulators 800-mA 15-V linear voltage regulator 800-mA 15-V linear voltage regulator";"";"";"";"1.8mm";"onsemi";"LM1117MPX-33NOPB";"863-LM1117MPX-33NOPB";"https://www.mouser.co.uk/ProductDetail/onsemi/LM1117MPX-33NO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";"";
"1";"LM2596SX-5.0_NOPB";"LM2596SX-5.0_NOPB";"KTT0005B";"IC1";"SIMPLE SWITCHER&#174; 4.5V to 40V, 3A Low Component Count Step-Down Regulator";"";"";"SIMPLE SWITCHER&#174";" 4.5V to 40V, 3A Low Component Count Step-Down Regulator";"";"";"";"mm";"Texas Instruments";"LM2596SX-5.0/NOPB";"926-LM2596SX-5.0NOPB";"https://www.mouser.co.uk/ProductDetail/Texas-Instruments/LM2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";
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
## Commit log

2024-06-15 FEAT: update sch, board, gerber adn bom for esp embedded to pcb
2024-06-16 DOC: update doc
2024-06-16 FIX: fix minor pcb
2024-06-18 FIX: fix gnd pin on ic 1117 that no connected
2024-06-18 FIX: fix led pin io2 ond katoda connected to 3v3 otherwise gns
2024-07-19 FIX: fix reverse transistor relay

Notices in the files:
parts and their libraries:
microbuilder: This work is placed in the public domain, and may be freely used for commercial and non-commercial work with the following conditions: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
